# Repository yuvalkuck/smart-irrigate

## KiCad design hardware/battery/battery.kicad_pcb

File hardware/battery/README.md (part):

# Battery add-on board

Schematic: `battery.kicad_sch` (one sheet, all blocks wired pin to pin). The sheet carries only the wire-colour legend and the block titles.
All the notes are here. This folder has no PCB yet.

The battery board is an add-on for the battery stage. V1 of the system runs without it: the mainboard takes 24 V DC from an
external supply at its J1 and makes its own +5V and 24 VAC (`hardware/mainboard/README.md`). When the add-on is
installed, the external 24 V DC supply moves to the add-on J1, and the add-on J5 feeds the mainboard J1.
Nothing is on both boards: the add-on holds the battery, its gauge and protector, its charger and the 24 V DC bus that
keeps the mainboard running on battery.

## Rails and sources

| Output | Connector | Value | Source |
|---|---|---|---|
| 24 V DC to the mainboard | J5 | 23.9 V typical, rated 2 A | LM5176 buck-boost (U6) |
| Pack charge | J2 | 20.82 V typical, 0.498 A | BQ24610 charger (U4) |

## How power flows

```
24 V PSU -- J1 -- F1 -- ideal diode U1/Q1 --+-- BUS (14 to 25 V)
                                             |
pack 5S -- J2 -- F2 -- Q3 (CHG) -- Q4 (DSG) -- PACKP -- ideal diode U2/Q2 --+
   B- (VSS) -- R69 (2 mohm) -- GND   (BQ40Z80 U3 drives Q3 and Q4, counts the current in R69)
                                             |
BUS --+-- U4 charger (21 V, 0.5 A) ----------> PACKP -> pack
      +-- U6 buck-boost -------------------> +24V (J5) -> mainboard J1
```

* The pack is 5S so that its full voltage (5 x 4.2 V = 21 V) stays below the 24 V supply. The two ideal diodes then switch sources by themselves, with no relay.
* BUS range is 14 V to 25 V. The lower limit is the cell under-voltage cut (2.8 V x 5 cells = 14 V); the BQ40Z80 limits are set in its data flash.
* U6 holds +24V at 23.9 V over the whole bus range, so the mainboard sees the same 24 V on mains and on battery.
* The charger is fed from BUS (after U1), not from the PSU node. It has no power-path mode, so the pack never feeds the PSU node through the charger.
* On mains, the charger takes only the 0.5 A set by its sense resistor R18. U6 takes the rest from the PSU through the same bus.
* Q3 and Q4 are high-side N-FETs with their drains joined in the middle (`MID`), as in the BQ40Z80 datasheet: CHG drives Q3 against the cell-stack side, DSG drives Q4 against the pack side.

## Connectors

| Ref | Pins | Use |
|---|---|---|
| J1 | 1 = 24 V in, 2 = GND | external 24 V DC supply |
| J2 | 1 = pack B+ (`BP`), 2 = pack B- (`VSS`) | pack power |
| J3 | 1 = B-, 2 to 5 = cell taps 1 to 4, 6 = B+, 7 = gauge `TS1`, 8 = charger `TS`, 9 = GND | pack sense (1x9 pin header, 2.54 mm): balance taps and the two 10 k NTCs (103AT) |
| J4 | 1 = +5V (from the mainboard), 2 = GND, 3 = +3V3 (from the mainboard), 4 = SDA, 5 = SCL, 6 = `MAINS_OK_N`, 7 = `STAT1`, 8 = `STAT2` | link to mainboard J16 (1x8 pin header, 2.54 mm, same pin order) |
| J5 | 1 = +24V, 2 = GND | 24 V DC out to mainboard J1 |

Pack B- (`VSS`) is not the same net as GND: the 2 mohm sense resistor R69 sits between them.
The gauge NTC returns to J3 pin 1 (B-), the charger NTC to J3 pin 9 (GND).

### Wiring the pack to J3

The pack is 5 cells in series (5S), cell 1 at the negative end. J3 only senses; the charge and discharge current goes through J2 (pin 1 = B+, pin 2 = B-).

| J3 pin | Connect to | Net, and where it goes |
|---|---|---|
| 1 | pack negative (cell 1 minus) | `VSS`, the same net as J2 pin 2; BQ40Z80 `VSS` |
| 2 | cell 1 plus (= cell 2 minus) | R64 to `VC1` |
| 3 | cell 2 plus (= cell 3 minus) | R65 to `VC2` |
| 4 | cell 3 plus (= cell 4 minus) | R66 to `VC3` |
| 5 | cell 4 plus (= cell 5 minus) | R67 to `VC4` |
| 6 | pack positive (cell 5 plus) | `BP`, the same net as J2 pin 1; R68 to `VC5` |
| 7 | one lead of the gauge NTC (10 k, 103AT); the other lead goes to pin 1 | BQ40Z80 `TS1` |
| 8 | one lead of the charger NTC (10 k, 103AT); the other lead goes to pin 9 | BQ24610 `TS`, with R25 and R26 |
| 9 | the other lead of the charger NTC | GND |

* Both NTCs sit on the pack.
* `VC6` of the BQ40Z80 is tied to `VC5`, so only the taps above are used.

## What the hardware reports to the mainboard

| Metric | Source | Reaches the mainboard on |
|---|---|---|
| Each cell voltage (5 cells), pack voltage | BQ40Z80, cell taps VC1 to VC5 | SMBus: J4 pins 4 and 5 |
| Pack current, both directions | BQ40Z80, coulomb counter on R69 | SMBus |
| Charge amount (remaining capacity, state of charge, full-charge capacity, cycle count) | BQ40Z80, Impedance Track gas gauge | SMBus (datasheet: "available capacity, voltage, current, temperature, and other critical parameters") |
| Pack temperature | BQ40Z80 `TS1` (the NTC on J3 pin 7); `TS2` to `TS4` are free | SMBus |
| Protection status (OV, UV, overcurrent, short circuit, temperature) | BQ40Z80 | SMBus |
| Charger state: charging, done, fault | BQ24610 `STAT1` and `STAT2` (open drain) | J4 pins 7 and 8 (pull-ups R65 and R66 are on the mainboard) |
| Mains present | BQ24610 `PG` (open drain) | J4 pin 6 (`MAINS_OK_N`, pull-up R64 on the mainboard) |

* `MAINS_OK_N`: low means BUS is above the pack, which means the supply is present. High means battery. If the pin sticks high, firmware sees "battery", which is the safe side.
* The BQ40Z80 SMBus pins (`SMBD`, `SMBC`) accept 1.3 V as high and 0.8 V as low (datasheet, electrical characteristics), so the 3.3 V pull-ups on the mainboard I2C bus are enough. Its SMBus speed is 10 to 100 kHz in slave mode, so the shared mainboard bus has to run at 100 kHz or below.
* The BQ40Z80 SMBus slave address is in its technical reference manual (SLUUBT5), which I have not read.
* Firmware items that follow from this (not changed here): read `MAINS_OK_N`, `STAT1` and `STAT2`, apply the 2-valve limit while `MAINS_OK_N` is high, and read the BQ40Z80 over SMBus.

## Block values

Source tags: D = value or part taken from the datasheet. C = computed with that datasheet's equation. T = start value, tune on the bench.

### Input and bus
* F1 is a 10 A 5x20 fuse at the input. U1/Q1 (PSU) and U2/Q2 (pack) are LM74700-Q1 ideal-diode controllers with DMT6007LFG FETs. C1 to C4 are the 100 nF charge-pump and anode capacitors (D).
* Bus capacitors: C5 220 uF polymer and C6 to C9, 4 x 10 uF.

### Battery gauge and protector (U3, BQ40Z80)
* 2-series to 6-series pack manager with gas gauging, protection, cell balancing and SMBus, VQFN-32 (datasheet SLUSBV4D). Used as 5S: `VC6` is tied to `VC5` ("if not used, connect to VC5", D).
* Cell taps: R64 to R68 (100 R) and C94 to C98 (100 nF) on `VC1` to `VC5`, as in the datasheet (D). The internal balancing FETs are 200 R, so the 100 R series resistors set the balance current (D).
* Current: R69 is a 2 mohm 1 W 50 ppm sense resistor in the pack minus lead, between `VSS` (the cell stack) and GND. The datasheet supports 1 to 3 mohm and wants 50 ppm or better (D). R70 and R71 (100 R) with C99 (100 pF) and C100/C101 (100 nF) filter `SRP` and `SRN` (D).
* Supply: `BAT` from `BP` through D5 and R72 (100 R); `VCC` from the middle of the FETs through D6 and R73 (100 R); `PACK` from the pack side through R74 (100 R). C102 (2.2 uF) on `PBI` (D). The two diodes and the series values are start values (T).
* FETs: Q3 (charge) and Q4 (discharge) are DMT6007LFG, 60 V. Gate resistors R75 and R77 (10 k) and gate-source resistors R76 and R78 (10 M), as in the datasheet (D). C103 and C104 (100 nF in series) across the pack terminals are the datasheet ESD pair.
* Temperature: the pack NTC (J3 pin 7) is on `TS1`. The BQ40Z80 has an internal 18 k pull-up for a 10 k 103 NTC (D), so no bias resistor is fitted.
* Unused pins: `TS2`, `TS3`, `TS4`, `DISP`, `PDSG`, `PRES`, `FUSE` are tied to `VSS` ("connect directly to VSS and configure data flash accordingly", D). `LEDCNTLA/B/C` go to `VSS` through R79, R80 and R81, 20 k each ("if not used, connect to VSS with a 20-kΩ resistor", D). `PCHG` is left open ("leave floating if not used", D). The pre-charge FET and the chemical fuse are not used.
* F2 is the 10 A fuse in the pack plus lead, between `BP` and the charge FET.
* One-time setup: the chip must be configured with TI bqStudio (cell count, chemistry, calibration; datasheet section 7.3.1) before the gauge readings are valid.

### Charger (U4, BQ24610)
* Charge voltage: R19 (909 k) and R20 (102 k), both 0.1 %, give 20.82 V typical, which is 4.16 V per cell. The worst case with tolerances is 20.96 V (4.19 V per cell). (C)
* Charge current: R18 (100 m) with ISET1 at 1.00 V gives about 0.50 A (R21 100 k over R22 43.2 k set 0.498 A). (C)
* Termination and pre-charge: R23 100 k over R24 17.8 k set about 49.9 mA. (C)
* C30 (100 nF) on `TTC` sets the safety timer to about 9.3 h. (D)
* NTC window 0 to 45 C: R25 9.31 k, R26 430 k, NTC at J3 pin 8. (D)
* L1 6.8 uH, Q5 (dual DMN6040SSD) as the two switches, D1 and C26 as the bootstrap.
* `STAT1` and `STAT2` (open drain) go to J4. The power-path pins and the input-current regulation are not used. This follows the BQ24610 datasheet's typical application without power path (section 10.2.2).

### 24 V DC (U6, LM5176)
* Input 14 V to 25 V, output 23.9 V (R36 309 k over R37 10.7 k), switching about 297 kHz (R32 27.4 k). L3 15 uH. (C)
* R29 is the 15 m sense resistor. The minimum boost current limit is about 6.7 A against a peak need of about 4.6 A at 2 A load. (C)
* Compensation R33 5.76 k, C40 82 nF, C41 680 pF, slope C38 390 pF, soft start C39 100 nF are start values. (T)
* Under-voltage lock-out: R34 249 k over R35 29.4 k turns it on at about 11.55 V (1.22 V typical `EN/UVLO` threshold). R38 (93.1 k) sets the hiccup mode.
* Q6 to Q9 are the four DMT6007LFG switches, D2 and D3 with C45 and C46 are the two bootstraps.

### Test points, LEDs and mounting holes
* Test points (2.0 mm through-hole pads, as on the mainboard): TP1 GND, TP2 `PSU_IN`, TP3 `BUS`, TP4 `PACKP` (pack +), TP5 `VSS` (pack minus, so the drop across R69 can be read against GND), TP6 `+24V` (output to the mainboard).
* Power-on LED DS7 (5 mm green): `BUS` through R88 (10 k) to GND, about 2 mA. `BUS` is live from either the PSU or the pack, so it shows that the board is powered. It stays on, and on battery it draws about 2 mA.
* SW1 "SHOW LEDs" lights all the rail LEDs while it is pressed. The cathodes of DS1 to DS6 are joined, and SW1 connects that node to GND. Nothing is drawn while the button is up. Each LED has a series resistor from its rail:

| LED (0805 red) | Rail | Resistor |
|---|---|---|
| DS1 | `PSU_IN` | R82, 10 k |
| DS2 | `BUS` | R83, 10 k |
| DS3 | `PACKP` | R84, 10 k |
| DS4 | `+24V` | R85, 10 k |
| DS5 | `+5V` (from the mainboard, J4) | R86, 1 k |
| DS6 | `+3V3` (from the mainboard, J4) | R87, 470 R |

* The resistor values are start values (T). I did not check the LED brightness on the bench.
* H1 to H4 are four M3 mounting holes (`MountingHole_3.2mm_M3`), with no net. The schematic has no PCB yet, so their positions are not set.
* The rails reach this block through net labels (`PSU_IN`, `BUS`, `PACKP`, `VSS`, `+24V`); `+5V` and `+3V3` are power symbols.

## Bill of materials (grouped by value)

Counts come from the schematic. Resistors and capacitors are 0805 unless the footprint says otherwise.
Reference numbers have gaps: the 5 V, 12 V, 45 V boost and inverter parts moved to the mainboard, and the BQ7791501 parts were replaced.

| Parts | Value / part | Footprint |
|---|---|---|
| U1, U2 | LM74700QDBVRQ1 | SOT-23-6 |
| U3 | BQ40Z80RSMR | VQFN-32 4x4 |
| U4 | BQ24610RGER | VQFN-24 |
| U6 | LM5176PWPR | HTSSOP-28 |
| Q1, Q2, Q3, Q4, Q6, Q7, Q8, Q9 | DMT6007LFG | PowerDI3333-8 |
| Q5 | DMN6040SSD-13 (dual) | SOIC-8 |
| D1, D2, D3, D5, D6 | MBR0540 | SOD-123 |
| L1 | 6.8 uH Coilcraft XAL1010-682ME | XAL1010 |
| L3 | 15 uH Coilcraft XAL1010-153ME | XAL1010 |
| F1, F2 | 10 A fuse, 5x20 holder | fuse holder |
| J1, J2, J5 | 2-pin screw terminal | 5.00 mm |
| J3 | 1x9 pin header | 2.54 mm |
| J4 | 1x8 pin header | 2.54 mm |
| TP1 to TP6 | test point pad | 2.0 mm THT, 1.0 mm drill |
| DS1 to DS6 | LED, red | 0805 |
| DS7 | LED, green | 5 mm THT |
| SW1 | push button "SHOW LEDs" | 6 mm THT |
| H1 to H4 | M3 mounting hole | 3.2 mm |

Capacitors:

| Parts | Value |
|---|---|
| C1 C2 C3 C4 C18 C19 C20 C25 C26 C42 C44 C103 C104 | 100 nF 50 V X7R (13) |
| C39 C45 C46 C94 C95 C96 C97 C98 C100 C101 | 100 nF 25 V X7R (10) |
| C30 | 100 nF 25 V X7R, 5 % |
| C27 C28 | 1 uF 25 V X7R |
| C17 | 1 uF 50 V X7R |
| C43 | 1 uF 16 V X7R |
| C102 | 2.2 uF 50 V X7R |
| C6 C7 C8 C9 C47 C48 C49 C50 C51 C52 C53 | 10 uF 50 V X7R, 1210 (11) |
| C21 C22 | 10 uF 35 V X7R, 1210 |
| C23 C24 | 4.7 uF 50 V X7R, 1210 |
| C5 | 220 uF 35 V polymer, 8x10 |
| C54 | 100 uF 35 V polymer, 8x10 |
| C40 | 82 nF |
| C37 C38 C41 | 47 pF / 390 pF / 680 pF |
| C29 / C99 | 22 pF / 100 pF |

Resistors:

| Parts | Value |
|---|---|
| R69 | 2 m 1 % 1 W 50 ppm, 2512 |
| R29 | 15 m 1 % 1 W, 2512 |
| R18 | 100 m 1 % 0.5 W, 1206 |
| R17, R39 | 10 R |
| R30 R31 R64 R65 R66 R67 R68 R70 R71 R72 R73 R74 | 100 R (12) |
| R87 | 470 R |
| R86 | 1 k |
| R33 | 5.76 k |
| R25 | 9.31 k |
| R75, R77, R82, R83, R84, R85, R88 | 10 k |
| R37 | 10.7 k |
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
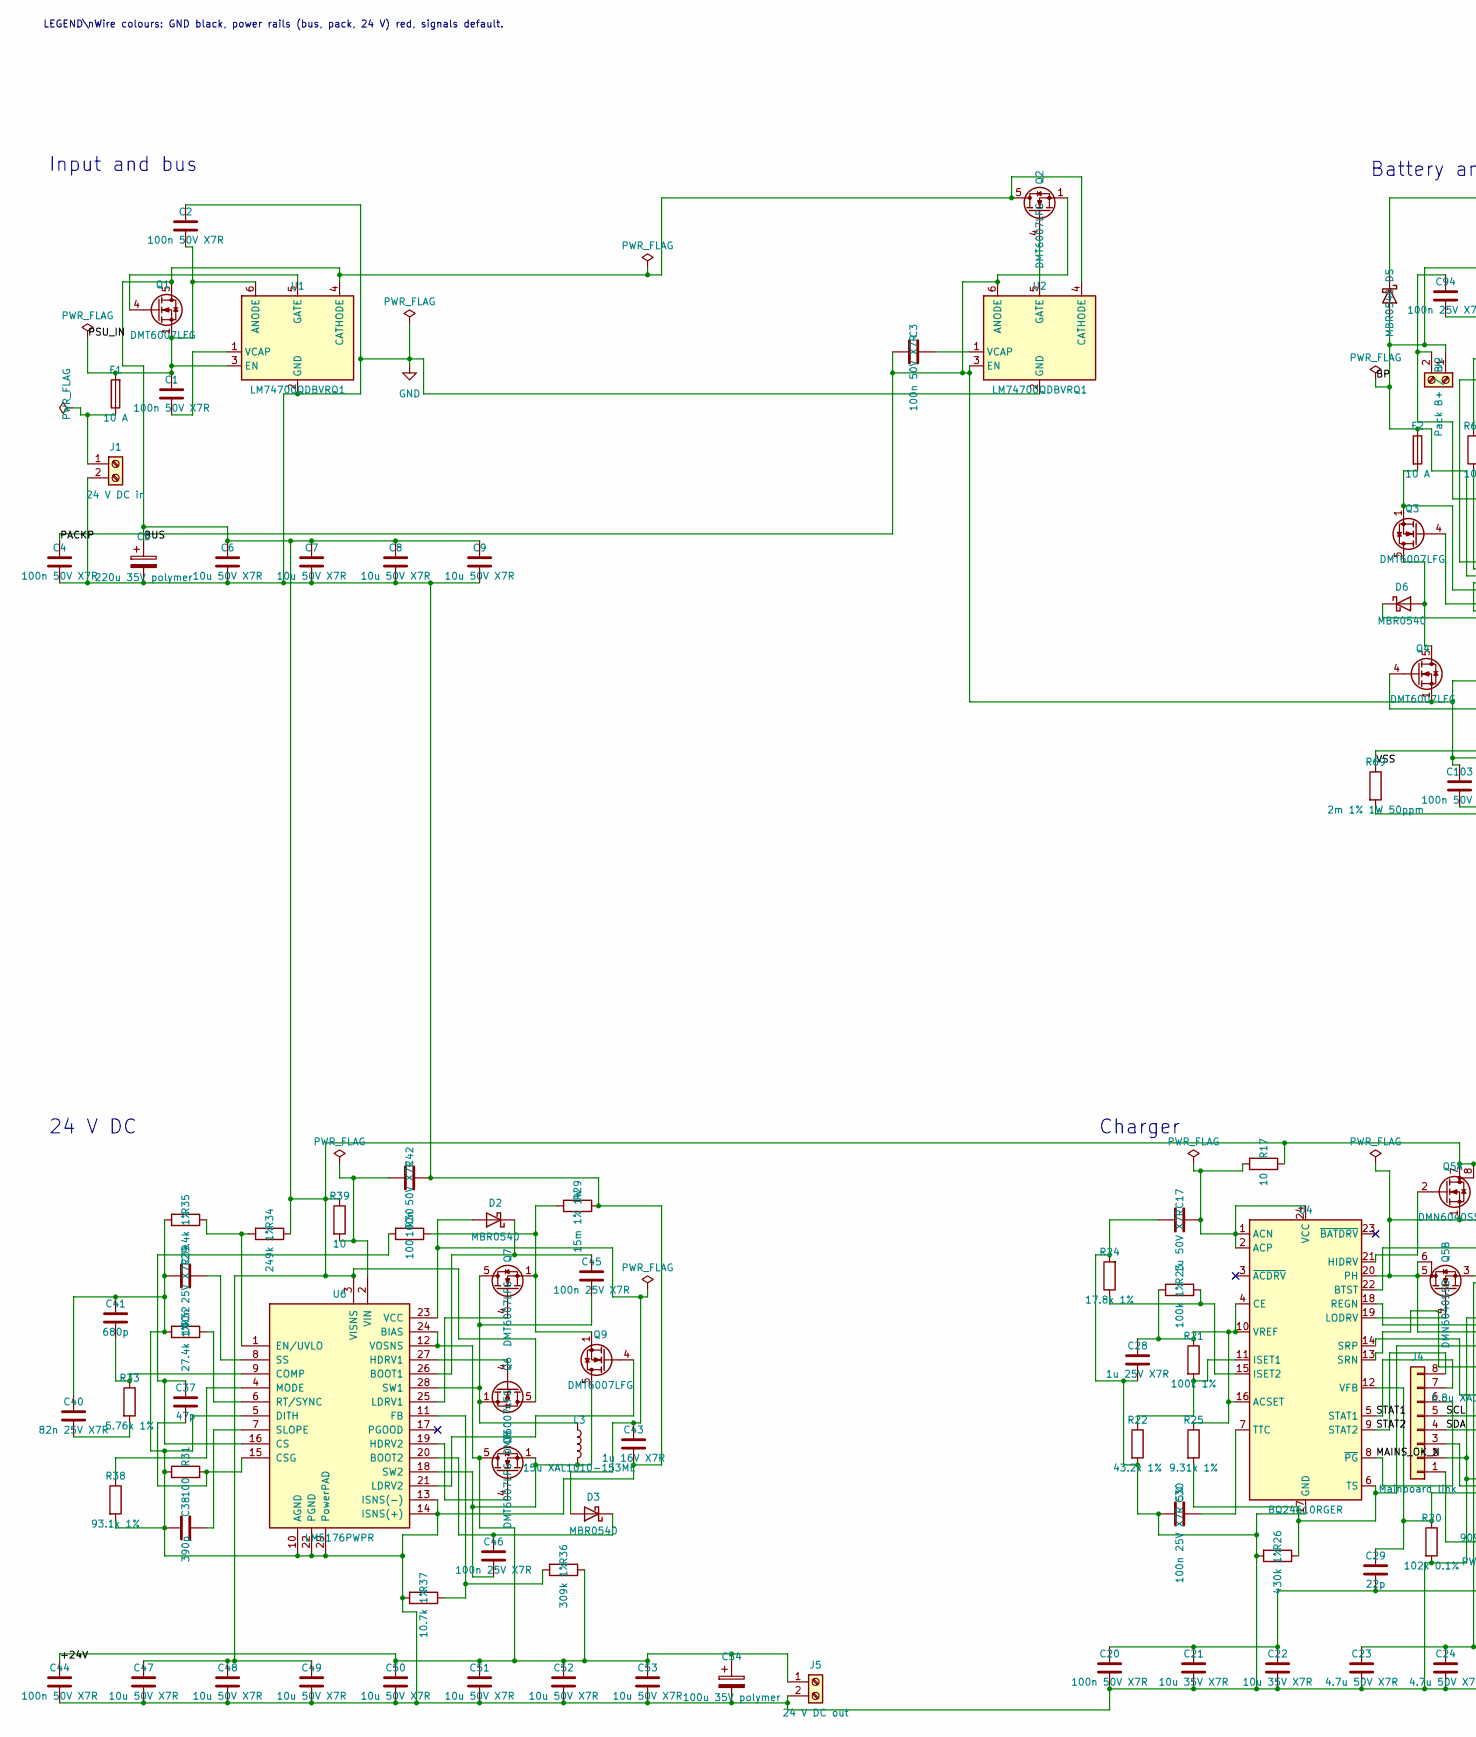
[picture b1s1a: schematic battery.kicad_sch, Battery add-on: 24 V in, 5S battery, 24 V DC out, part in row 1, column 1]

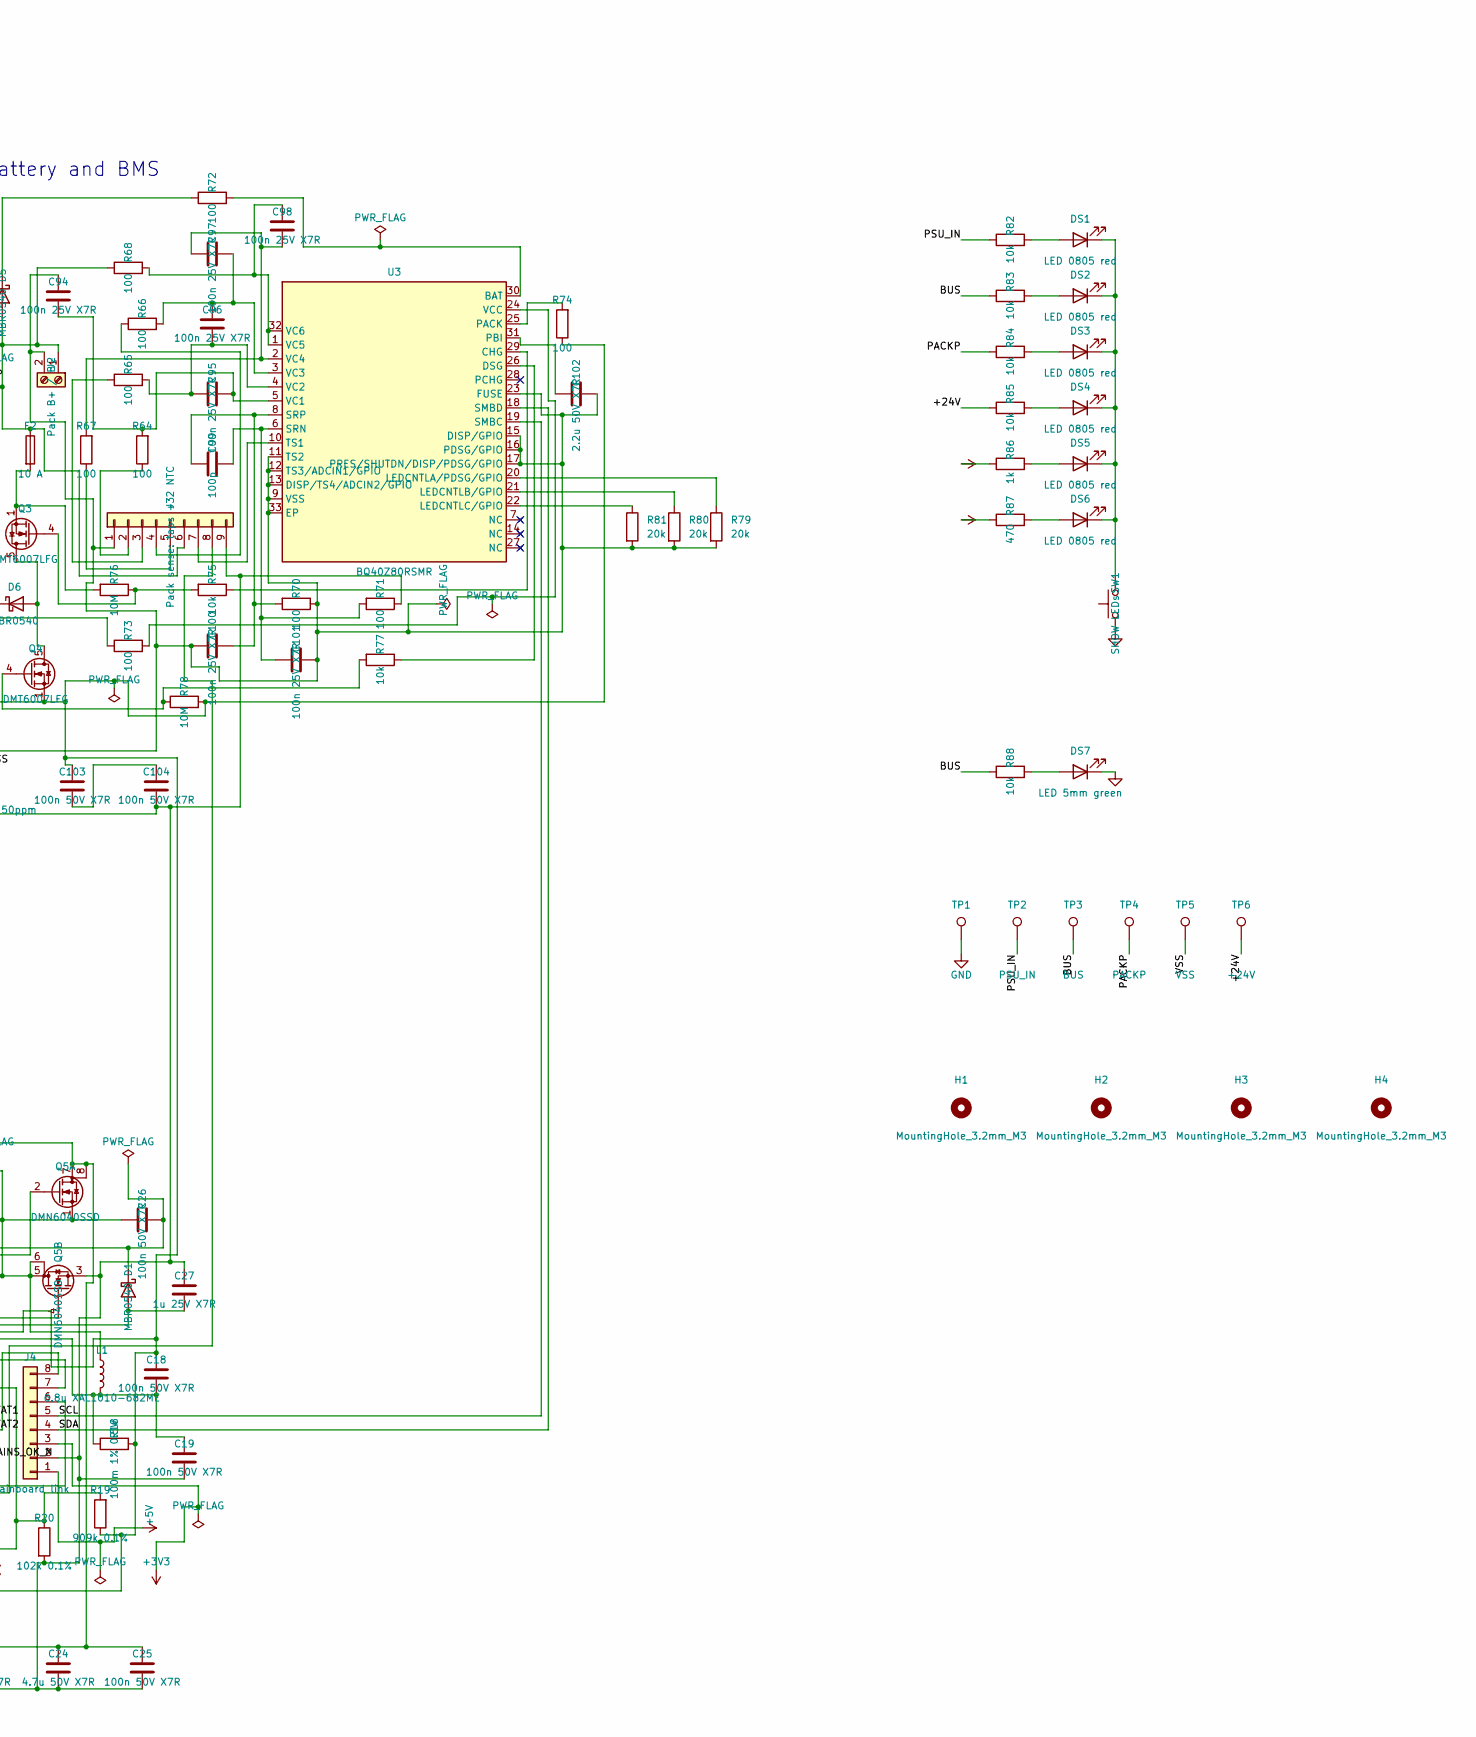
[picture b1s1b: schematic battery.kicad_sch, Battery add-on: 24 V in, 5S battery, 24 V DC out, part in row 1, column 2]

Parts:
C1, C2, C3, C4, C18, C19, C20, C25, C26, C42, C44, C103, C104: 100n 50V X7R
C5: 220u 35V polymer
C6, C7, C8, C9, C47, C48, C49, C50, C51, C52, C53: 10u 50V X7R
C17: 1u 50V X7R
C21, C22: 10u 35V X7R
C23, C24: 4.7u 50V X7R
C27, C28: 1u 25V X7R
C29: 22p
C30: 100n 25V X7R 5%
C37: 47p
C38: 390p
C39, C45, C46, C94, C95, C96, C97, C98, C100, C101: 100n 25V X7R
C40: 82n 25V X7R
C41: 680p
C43: 1u 16V X7R
C54: 100u 35V polymer
C99: 100p
C102: 2.2u 50V X7R
D1, D2, D3, D5, D6: MBR0540
DS1, DS2, DS3, DS4, DS5, DS6: LED 0805 red
DS7: LED 5mm green
F1, F2: 10 A
H1, H2, H3, H4: MountingHole_3.2mm_M3
J1: 24 V DC in
J2: Pack B+ / B-
J3: Pack sense: taps + 2 NTC
J4: Mainboard link
J5: 24 V DC out
L1: 6.8u XAL1010-682ME
L3: 15u XAL1010-153ME
Q1, Q2, Q3, Q4, Q6, Q7, Q8, Q9: DMT6007LFG; Diodes_PowerDI3333-8
Q5: DMN6040SSD
R17, R39: 10
R18: 100m 1% 0.5W
R19: 909k 0.1%
R20: 102k 0.1%
R21, R23: 100k 1%
R22: 43.2k 1%
R24: 17.8k 1%
R25: 9.31k 1%
R26: 430k 1%
R29: 15m 1% 1W
R30, R31, R64, R65, R66, R67, R68, R70, R71, R72, R73, R74: 100
R32: 27.4k 1%
R33: 5.76k 1%
R34: 249k 1%
R35: 29.4k 1%
R36: 309k 1%
R37: 10.7k 1%
R38: 93.1k 1%
R69: 2m 1% 1W 50ppm
R75, R77, R82, R83, R84, R85, R88: 10k
R76, R78: 10M
R79, R80, R81: 20k
R86: 1k
R87: 470
SW1: SHOW LEDs
TP1: GND
TP2: PSU_IN
TP3: BUS
TP4: PACKP
TP5: VSS
TP6: +24V
U1, U2: LM74700QDBVRQ1; SOT-23-6
U3: BQ40Z80RSMR; VQFN-32-1EP_4x4mm_P0.4mm_EP2.8x2.8mm
U4: BQ24610RGER; VQFN-24-1EP_4x4mm_P0.5mm_EP2.45x2.45mm
U6: LM5176PWPR; HTSSOP-28-1EP_4.4x9.7mm_P0.65mm_EP3.4x9.5mm_ThermalVias

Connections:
+3V3: J4.3, R87.1
+5V: J4.1, R86.1
/+24V: C44.1, C50.1, C51.1, C52.1, C53.1, C54.1, J5.1, Q8.5 (D), R36.1, R85.1, TP6.1 (1_1), U6.12 (VOSNS), U6.24 (BIAS)
/BP: D5.2 (A), F2.1, J2.1, J3.6, R68.1
/BUS: C5.1, C6.1, C7.1, C8.1, C9.1, C23.1, C24.1, C25.1, C47.1, C48.1, C49.1, Q1.5 (D), Q2.5 (D), Q5.7 (D), Q5.8 (D), Q6.5 (D), R17.1, R34.1, R39.1, R83.1, R88.1, TP3.1 (1_1), U1.4 (CATHODE), U2.4 (CATHODE), U6.3 (VISNS)
/MAINS_OK_N: J4.6, U4.8 (~PG)
/PACKP: C3.1, C4.1, C18.2, C20.1, C21.1, C22.1, C29.1, C103.1, Q2.1 (S), Q2.2 (S), Q2.3 (S), Q4.1 (S), Q4.2 (S), Q4.3 (S), R18.2, R19.1, R74.1, R78.2, R84.1, TP4.1 (1_1), U2.3 (EN), U2.6 (ANODE), U4.13 (SRN)
/PSU_IN: C1.1, C2.1, F1.2, Q1.1 (S), Q1.2 (S), Q1.3 (S), R82.1, TP2.1 (1_1), U1.3 (EN), U1.6 (ANODE)
/SCL: J4.5, U3.19 (SMBC)
/SDA: J4.4, U3.18 (SMBD)
/STAT1: J4.7, U4.5 (STAT1)
/STAT2: J4.8, U4.9 (STAT2)
/VSS: C94.2, C100.2, C101.2, C102.2, J2.2, J3.1, R69.1, R70.1, R79.2, R80.2, R81.2, TP5.1 (1_1), U3.9 (VSS), U3.11 (TS2), U3.12 (TS3/ADCIN1/GPIO), U3.13 (DISP/TS4/ADCIN2/GPIO), U3.15 (DISP/GPIO), U3.16 (PDSG/GPIO), U3.17 (PRES/SHUTDN/DISP/PDSG/GPIO), U3.23 (FUSE), U3.33 (EP)
GND: C2.2, C4.2, C5.2, C6.2, C7.2, C8.2, C9.2, C17.2, C19.2, C20.2, C21.2, C22.2, C23.2, C24.2, C25.2, C27.2, C28.2, C30.2, C38.2, C39.2, C40.2, C41.2, C42.2, C43.2, C44.2, C47.2, C48.2, C49.2, C50.2, C51.2, C52.2, C53.2, C54.2, C104.2, DS7.1 (K), J1.2, J3.9, J4.2, J5.2, Q5.3 (S), R20.2, R22.2, R24.2, R26.2, R29.2, R31.1, R32.2, R35.2, R37.2, R38.2, R69.2, R71.1, SW1.1, TP1.1 (1_1), U1.2 (GND), U2.2 (GND), U4.17 (GND), U4.25 (GND), U6.5 (DITH), U6.10 (AGND), U6.13 (ISNS(-)), U6.14 (ISNS(+)), U6.22 (PGND), U6.29 (PowerPAD)
unnamed: C40.1, R33.2
unnamed: C103.2, C104.1
unnamed: C27.1, D1.2 (A), U4.18 (REGN)
unnamed: C26.1, D1.1 (K), U4.22 (BTST)
unnamed: C43.1, D2.2 (A), D3.2 (A), U6.23 (VCC)
unnamed: C45.1, D2.1 (K), U6.26 (BOOT1)
unnamed: C46.1, D3.1 (K), U6.20 (BOOT2)
unnamed: D5.1 (K), R72.1
unnamed: D6.2 (A), Q3.5 (D), Q4.5 (D)
unnamed: D6.1 (K), R73.1
unnamed: DS1.2 (A), R82.2
unnamed: DS1.1 (K), DS2.1 (K), DS3.1 (K), DS4.1 (K), DS5.1 (K), DS6.1 (K), SW1.2
unnamed: DS2.2 (A), R83.2
unnamed: DS3.2 (A), R84.2
unnamed: DS4.2 (A), R85.2
unnamed: DS5.2 (A), R86.2
unnamed: DS6.2 (A), R87.2
unnamed: DS7.2 (A), R88.2
unnamed: F2.2, Q3.1 (S), Q3.2 (S), Q3.3 (S), R76.2
unnamed: F1.1, J1.1
unnamed: J3.2, R64.1
unnamed: J3.3, R65.1
unnamed: J3.4, R66.1
unnamed: J3.5, R67.1
unnamed: J3.7, U3.10 (TS1)
unnamed: J3.8, R25.2, R26.1, U4.6 (TS)
unnamed: Q1.4 (G), U1.5 (GATE)
unnamed: Q2.4 (G), U2.5 (GATE)
unnamed: Q3.4 (G), R75.2, R76.1
unnamed: Q4.4 (G), R77.2, R78.1
unnamed: Q5.2 (G), U4.21 (HIDRV)
unnamed: C26.2, L1.1, Q5.1 (S), Q5.5 (D), Q5.6 (D), U4.20 (PH)
unnamed: Q5.4 (G), U4.19 (LODRV)
unnamed: Q6.4 (G), U6.27 (HDRV1)
unnamed: C45.2, L3.1, Q6.1 (S), Q6.2 (S), Q6.3 (S), Q7.5 (D), U6.28 (SW1)
unnamed: Q7.4 (G), U6.25 (LDRV1)
unnamed: Q7.1 (S), Q7.2 (S), Q7.3 (S), Q9.1 (S), Q9.2 (S), Q9.3 (S), R29.1, R30.1
unnamed: Q8.4 (G), U6.19 (HDRV2)
unnamed: C46.2, L3.2, Q8.1 (S), Q8.2 (S), Q8.3 (S), Q9.5 (D), U6.18 (SW2)
unnamed: Q9.4 (G), U6.21 (LDRV2)
unnamed: C1.2, U1.1 (VCAP)
unnamed: C3.2, U2.1 (VCAP)
unnamed: R72.2, U3.30 (BAT)
unnamed: R75.1, U3.29 (CHG)
unnamed: R77.1, U3.26 (DSG)
unnamed: R79.1, U3.20 (LEDCNTLA/PDSG/GPIO)
unnamed: R80.1, U3.21 (LEDCNTLB/GPIO)
unnamed: R81.1, U3.22 (LEDCNTLC/GPIO)
unnamed: R74.2, U3.25 (PACK)
unnamed: C102.1, U3.31 (PBI)
unnamed: C99.2, C101.1, R71.2, U3.6 (SRN)
unnamed: C99.1, C100.1, R70.2, U3.8 (SRP)
unnamed: C94.1, C95.2, R64.2, U3.5 (VC1)
unnamed: C95.1, C96.2, R65.2, U3.4 (VC2)
unnamed: C96.1, C97.2, R66.2, U3.3 (VC3)
unnamed: C97.1, C98.2, R67.2, U3.2 (VC4)
unnamed: C98.1, R68.2, U3.1 (VC5), U3.32 (VC6)
unnamed: R73.2, U3.24 (VCC)
unnamed: C17.1, R17.2, U4.1 (ACN), U4.2 (ACP), U4.24 (VCC)
unnamed: C28.1, R21.1, R23.1, R25.1, U4.4 (CE), U4.10 (VREF), U4.16 (ACSET)
unnamed: R21.2, R22.1, U4.11 (ISET1)
unnamed: R23.2, R24.1, U4.15 (ISET2)
unnamed: C18.1, C19.1, L1.2, R18.1, U4.14 (SRP)
unnamed: C30.1, U4.7 (TTC)
unnamed: C29.2, R19.2, R20.1, U4.12 (VFB)
unnamed: C41.1, R33.1, U6.9 (COMP)
unnamed: C37.1, R30.2, U6.16 (CS)
unnamed: C37.2, R31.2, U6.15 (CSG)
unnamed: R34.2, R35.1, U6.1 (EN/UVLO)
unnamed: R36.2, R37.1, U6.11 (FB)
unnamed: R38.1, U6.4 (MODE)
unnamed: R32.1, U6.6 (RT/SYNC)
unnamed: C38.1, U6.7 (SLOPE)
unnamed: C39.1, U6.8 (SS)
unnamed: C42.1, R39.2, U6.2 (VIN)

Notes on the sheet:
Input and bus
LEGEND\nWire colours: GND black, power rails (bus, pack, 24 V) red, signals default.
Charger
24 V DC
Battery and BMS

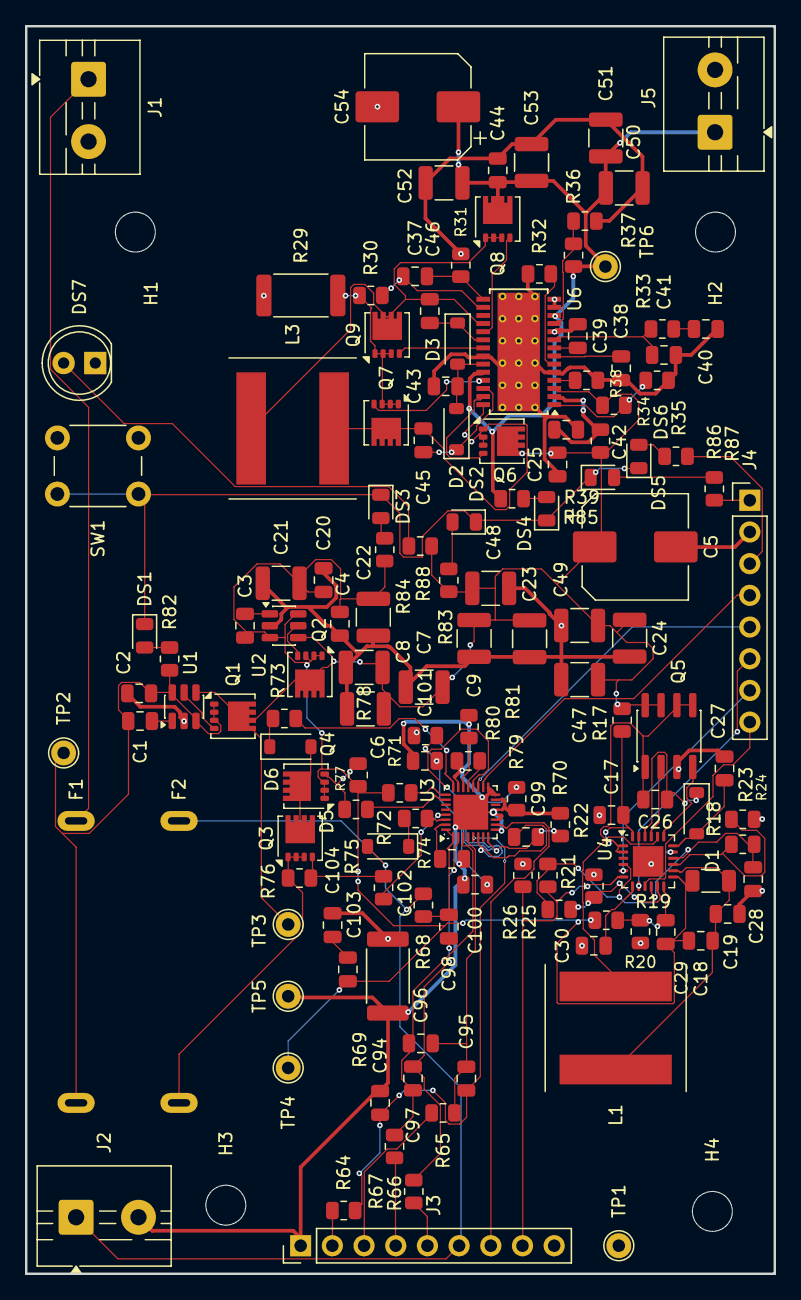
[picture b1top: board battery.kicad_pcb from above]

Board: 2 copper layers, 60.0 x 100.0 mm, 144 parts (0 on the bottom side), 89 nets.

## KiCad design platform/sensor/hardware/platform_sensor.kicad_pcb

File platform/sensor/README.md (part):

# Sensor Platform

Firmware project for the **sensor cluster**, the outdoor node on the sensor mast. It is a separate
STM32CubeMX project (`sensor_platform.ioc`), not part of the ESP-IDF build. The board is in
`hardware/kicad/`.

The node reads the local sensors and answers the ESP32-C6 over RS-485. The C6 is the Modbus master
and polls the cluster; the cluster never sends on its own.

## Hardware

| Item | Value |
|---|---|
| MCU | STM32C011F6P3TR (TSSOP-20, 32 KB flash, 6 KB RAM), matches `Mcu.CPN` in the `.ioc` |
| Clock | Internal, 12 MHz (as set in the `.ioc`) |
| Logic supply | 3.3 V from U3 (AP2112K-3.3), fed from the incoming 5 V |
| Bus transceiver | U2 MAX3485EPA (DIP-8) |
| Bus protection | D1 SM712 on A/B behind R11 and R12 (10 ohm, 1206, in series with A and B), D2 SMAJ5.0A on 5 V |
| Sensor-side protection | D6 SMAJ5.0A across AIN and GND, D7 and D8 (3.3 V bidirectional ESD diodes, SOD-523) on SDA and SCL |
| Cable shield | J1 and J4 pin 5 (SHLD) go to GND through R13 (1 M) in parallel with C9 (1 nF, 1 kV) |
| Input fuse | F1, 5x20 mm fuse (500 mA) in the ELECAPITAL PCB holder (footprint `libraries:FuseHolder_5x20_ELECAPITAL_PCB_Cover`), between the raw 5 V input and D2/FB1. J1.3 and J4.3 are before the fuse, so a daisy-chained node is not fused by this one. |
| Input filter | FB1 470 ohm ferrite on the 5 V, C8 47 uF bulk |
| Indicators | D3 green on 3.3 V (R10 1 k), D4 yellow on TX and D5 yellow on RX (R8, R9 1 k, lit when the line is low) |
| Wind input | J8 (library `WindSensor_0_5V`: 1 = +24V, 2 = GND, 3 = OUT). OUT goes through R14 (1.8 k) and R15 (3.3 k) to PA4, so 0-5 V becomes 0-3.24 V. D9 SMAJ30A on +24V, D10 SMAJ5.0A on OUT. The same wind sensor can instead connect to the mainboard. |
| Mode switch | SW1, 2-position DIP switch. Switch 1 fits the 120 ohm terminator R6 across A and B. Switch 2 pulls PA5 to GND to show that the wind sensor is fitted here. |
| Test points | TP1 +5V, TP2 +3V3, TP3 GND, TP4 A, TP5 B |
| Mounting | H1-H4, M3 holes (3.2 mm) |

Protection is for ESD and small induced surges only. A direct or very near lightning strike is not
covered: that needs a grounded mast with a lightning rod and the cable shield earthed at one end.

Power arrives from the main box on its own twisted pair. The board does not use 24 V itself. J1 and J4
pin 6 carry an optional +24V pass-through, for the wind sensor on J8 or for the next node. It is not
fused on this board, and it is left empty when no wind sensor is connected.

### Sensors

| Sensor | Interface | Purpose |
|---|---|---|
| SHT41 | I2C1 (J2, own connector) | Air temperature and relative humidity, for vapor pressure deficit |
| BMP581 | I2C1 (J7, own connector) | Barometric pressure and temperature, for rain-front prediction |
| Solar panel (0.3 W, 5 V polysilicon epoxy module) | ADC, PA0 (J6, own connector) | Sunlight level, for solar load |
| Wind sensor (3-cup, 0-30 m/s, 10-30 V supply, 0-5 V output) | ADC, PA4 (J8, own connector) | Wind speed. Optional: it can connect here or to the mainboard, selected by the hardware enable mask (`SensorWindPlatform`) |

The TSL2591 is dropped from the design. SHT41 and BMP581 sit in a ventilated radiation shield and
each connect over a short I2C cable, SHT41 to J2 and BMP581 to J7. The two connectors are in parallel on
the same I2C1 bus. I2C pull-ups (R1, R2, 4.7 k) go to 3.3 V, so both sensors run at 3.3 V logic.

## Pin map

From the netlist of `hardware/kicad/sensor-cluster.kicad_sch`.

| U1 pin | Function | Net |
|---|---|---|
| 1 | I2C1_SDA | J2 pin 4, J7 pin 2, R1 pull-up |
| 20 | I2C1_SCL | J2 pin 3, J7 pin 3, R2 pull-up |
| 7 (PA0) | ADC1_IN0 | Solar divider |
| 8 (PA1) | USART2_DE | U2 DE and /RE, R7 10 k to GND |
| 9 (PA2) | USART2_TX | U2 DI |
| 10 (PA3) | USART2_RX | U2 RO |
| 18 | SWDIO | J5 pin 2 |
| 19 | SWCLK | J5 pin 3 |
| 6 | NRST | J5 pin 4, C3 100 nF |
| 11 (PA4) | ADC input | Wind divider R14/R15 on J8 OUT, also on J3 pin 3 |
| 12 (PA5) | Input with pull-up | SW1 switch 2 to GND (ON = wind fitted), also on J3 pin 4 |
| 13-17, 2, 3 | unused | J3 breakout (PA6-PA10, PC14, PC15) |

DE and /RE are tied together and driven by the USART2 DE output (hardware driver-enable).

### Connectors

| Ref | Pins |
|---|---|
| J1 (6-pin terminal, 5.00 mm) | 1 = A, 2 = B, 3 = +5 V, 4 = GND, 5 = SHLD (cable shield), 6 = +24V (optional, wind sensor only) |
| J4 (6-pin terminal, 5.00 mm) | Same pins as J1, wired in parallel with it, to daisy-chain the bus to another node. The +5 V pin is the raw input, before D2 and FB1. |
| J8 (wind sensor terminal) | 1 = +24V, 2 = GND, 3 = OUT. The library footprint has 4 terminals, and terminal 4 has no net. |
| J2 (SHT41 module, library `SHT41_I2C_Module`) | 1 = VCC (3.3 V), 2 = GND, 3 = SCL, 4 = SDA |
| J7 (4-pin 2.54 mm row) | BMP581: 1 = GND, 2 = SDA, 3 = SCL, 4 = 3.3 V out |
| J6 (2-pin 2.54 mm row) | Solar panel, two wires: 1 = + (AIN), 2 = - (GND) |
| J5 (5-pin 2.54 mm row) | SWD programming: 1 = 3.3 V, 2 = SWDIO, 3 = SWCLK, 4 = NRST, 5 = GND |
| J3 (10-pin 2.54 mm row) | Breakout of the unused MCU pins: 1 = PC14, 2 = PC15, 3 = PA4, 4 = PA5, 5 = PA6, 6 = PA7, 7 = PA8, 8 = PA9, 9 = PA10, 10 = GND. 3.3 V only. |
| SW1 (2-position DIP switch) | Switch 1 (pins 1 and 4) fits the 120 ohm terminator R6 across A and B. Turn it on at the bus end only. Switch 2 (pins 2 and 3) pulls PA5 to GND when the wind sensor is fitted. |

Only AIN tolerates 5 V. SDA, SCL and the SWD pins are 3.3 V only.

### Solar input

The panel connects to J6 (AIN and GND). R5 (22 ohm, 1206, 0.25 W) across AIN and GND is the shunt, so
the panel current becomes a voltage. R3 (10 k) and R4 (15 k) divide it by 0.6 to the PA0 input, with
C7 (100 nF) as filter. Full scale at the pin is 3.0 V for 5.0 V at AIN. The panel current in watts is
only a relative sunlight measure, so calibrate it against a reference.

The panel is a generic DIY solar charger module. Specification from the listing:

| Item | Value |
|---|---|
| Power | 0.3 W |
| Material | Polycrystalline silicon, epoxy board |
| Voltage | 5 V |
| Operating current | 0-60 mA |
| Size | 68 x 36 mm |

The listing gives no open-circuit voltage. At the full 60 mA, R5 drops 1.32 V and dissipates about
80 mW, well inside its 0.25 W rating. PA0 then sees about 0.8 V, about 26 % of the 3.0 V full scale.
Keep this in mind when calibrating: a larger R5 would use more of the ADC range, but it also raises
the panel voltage, so it is not changed yet.

## Power consumption

Datasheet values, at the supply voltage stated for each row. Rows marked **not verified** have no figure
yet: the ST and Analog Devices sites would not serve the datasheet. The board has not been measured.

| Part | Condition | Current | Source |
|---|---|---|---|
| U3 AP2112K-3.3 | Quiescent, no load, VIN = 2.5 V | 55 uA typ, 80 uA max | Diodes AP2112 datasheet |
| SHT41 | Idle | 0.1 uA typ, 1.0 uA max (25 C) | Sensirion SHT4x datasheet |
| SHT41 | While measuring | 350 uA typ, 500 uA max | Sensirion SHT4x datasheet |
| SHT41 | Average, one measurement per second | 0.4 uA (medium repeatability) to 2.4 uA (high) | Sensirion SHT4x datasheet |
| BMP581 | Standby (25 C) | 1.0 uA | Bosch BMP581 datasheet |
| BMP581 | Low-power mode, 1 Hz | 1.3 uA | Bosch BMP581 datasheet |
| U1 STM32C011F6P3TR | Run at 12 MHz | **not verified** | ST datasheet |
| U2 MAX3485EPA | Supply current, driver on and off | **not verified** | Analog Devices datasheet |
| D3 green LED | Always on, R10 1 k | about 1.3 mA | Calculated, assumes 2 V forward voltage |
| D4, D5 yellow LEDs | Only while TX or RX is low, R8 and R9 1 k | about 1.3 mA each while lit | Calculated, assumes 2 V forward voltage |

All parts except the 5 V pair are fed from 3.3 V through U3, so the 5 V current at J1 is the sum of
these plus U3's own quiescent current (a linear regulator passes the load current through).

The total is not computed because U1 and U2 are missing. Measure it on the built board with a meter in
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
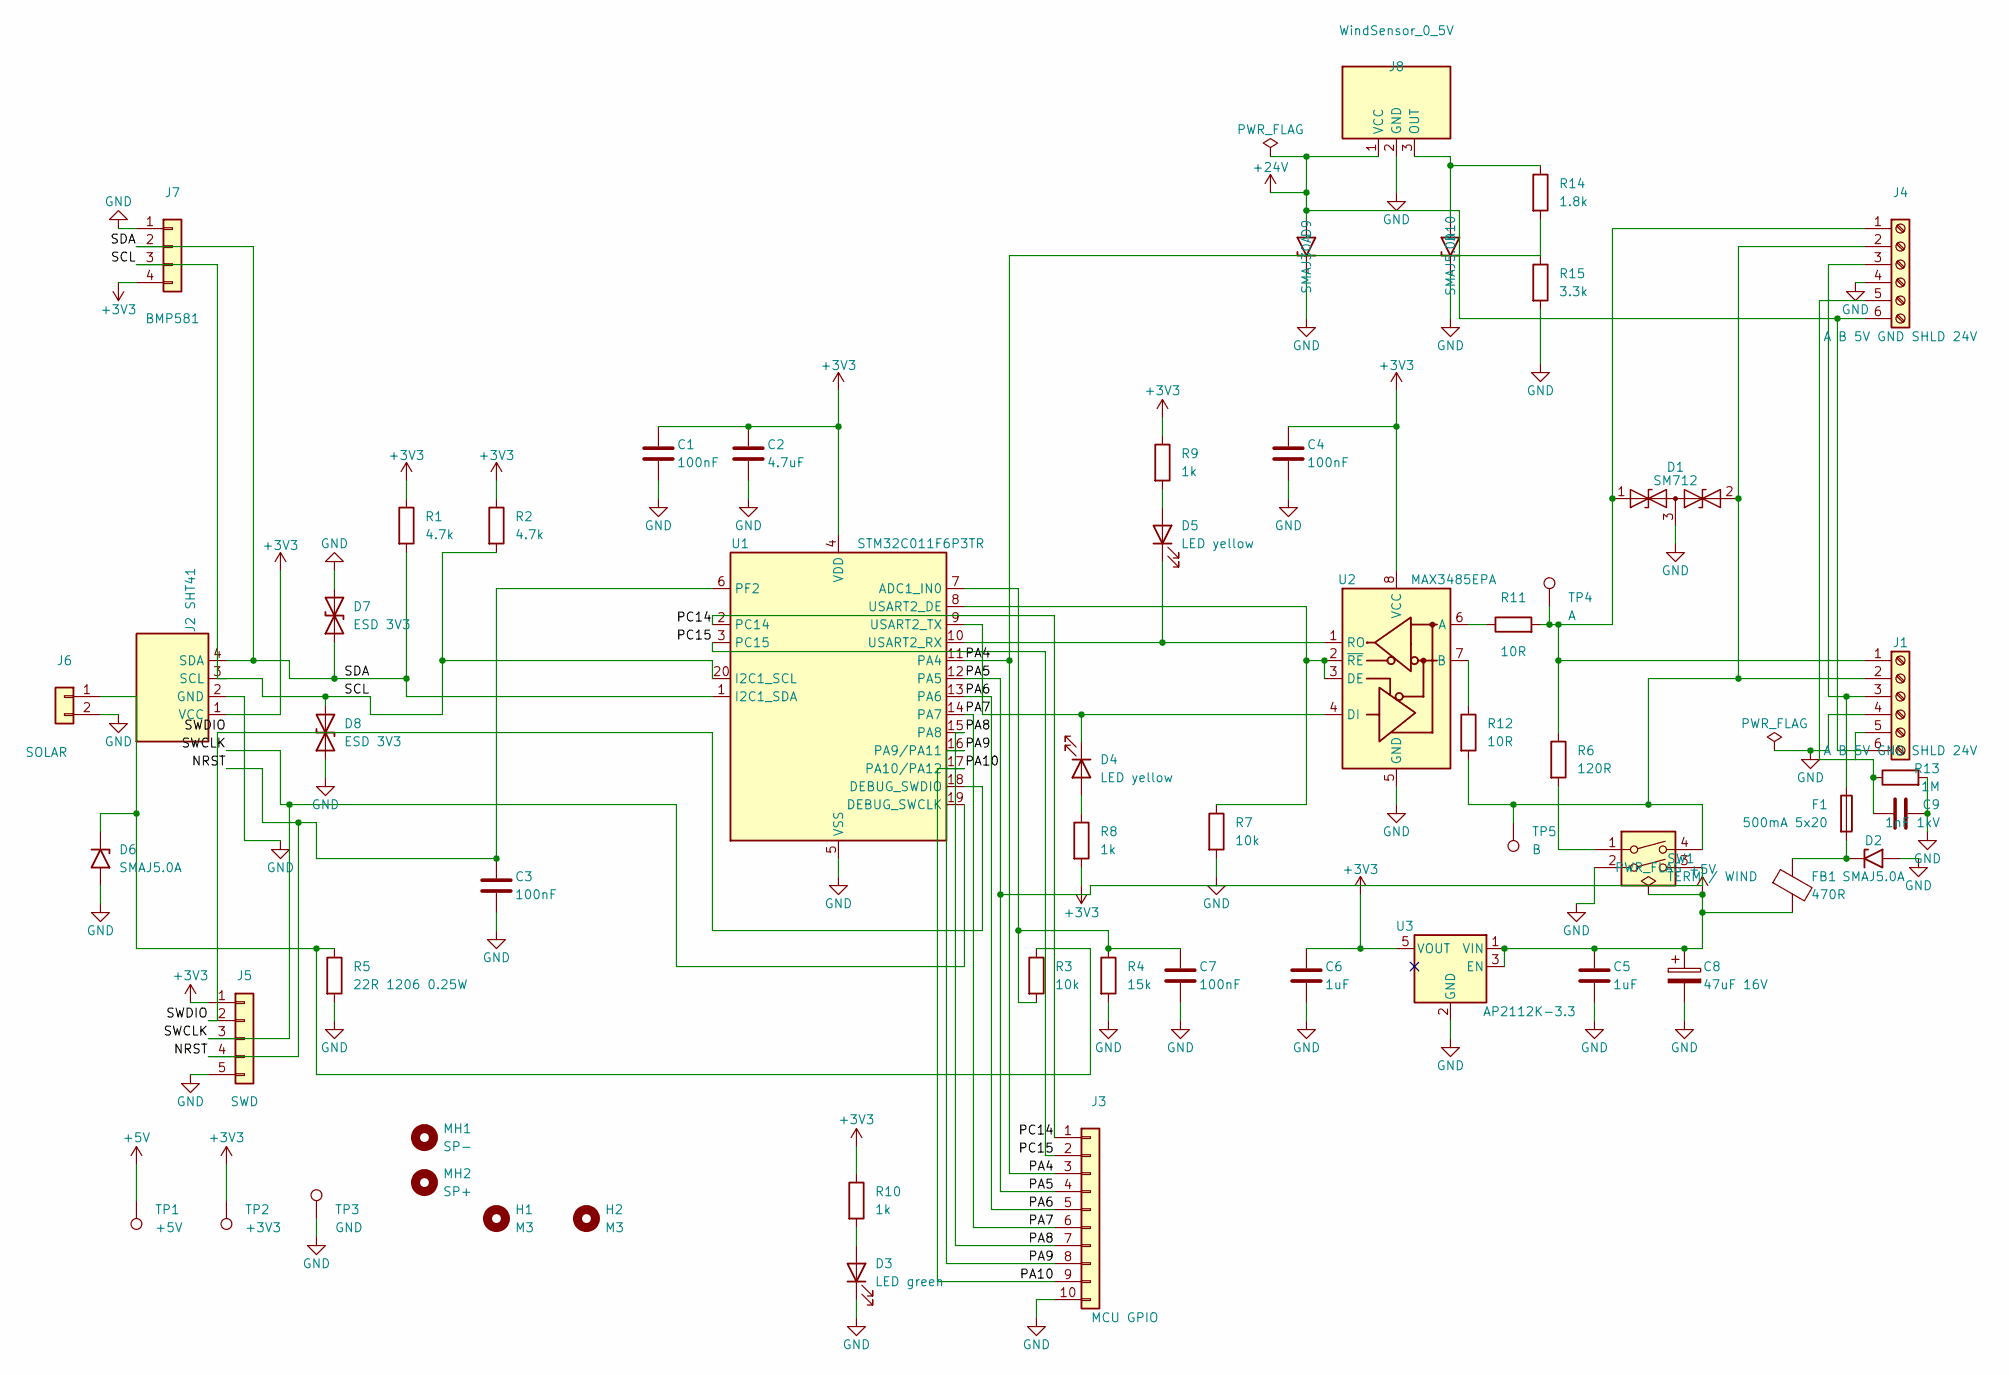
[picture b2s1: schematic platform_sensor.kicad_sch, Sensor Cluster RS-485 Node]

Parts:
C1, C3, C4, C7: 100nF; C_0805_2012Metric
C2: 4.7uF; C_0805_2012Metric
C5, C6: 1uF; C_0805_2012Metric
C8: 47uF 16V; CP_Elec_6.3x5.4
C9: 1nF 1kV; C_1206_3216Metric
D1: SM712; SOT-23
D2, D6, D10: SMAJ5.0A; D_SMA
D3: LED green; LED_0805_2012Metric
D4, D5: LED yellow; LED_0805_2012Metric
D7, D8: ESD 3V3; D_SOD-523
D9: SMAJ30A; D_SMA
F1: 500mA 5x20; FuseHolder_5x20_ELECAPITAL_PCB_Cover
FB1: 470R; L_0805_2012Metric
H1, H2: M3; MountingHole_3.2mm_M3
J1, J4: A B 5V GND SHLD 24V; TerminalBlock_MaiXu_MX126-5.0-06P_1x06_P5.00mm
J2: SHT41; PinHeader_1x04_P2.54mm_Vertical
J3: MCU GPIO; PinHeader_1x10_P2.54mm_Vertical
J5: SWD; PinHeader_1x05_P2.54mm_Vertical
J6: SOLAR; PinHeader_1x02_P2.54mm_Vertical
J7: BMP581; PinHeader_1x04_P2.54mm_Vertical
J8: WindSensor_0_5V; TerminalBlock_MaiXu_MX126-5.0-04P_1x04_P5.00mm
MH1: SP-; MountingHole_2.2mm_M2_DIN965_Pad
MH2: SP+; MountingHole_2.2mm_M2_DIN965_Pad
R1, R2: 4.7k; R_0805_2012Metric
R3, R7: 10k; R_0805_2012Metric
R4: 15k; R_0805_2012Metric
R5: 22R 1206 0.25W; R_1206_3216Metric
R6: 120R; R_0805_2012Metric
R8, R9, R10: 1k; R_0805_2012Metric
R11, R12: 10R; R_1206_3216Metric
R13: 1M; R_0805_2012Metric
R14: 1.8k; R_0805_2012Metric
R15: 3.3k; R_0805_2012Metric
SW1: TERM / WIND; SW_DIP_SPSTx02_Slide_9.78x7.26mm_W7.62mm_P2.54mm
TP1: +5V; TestPoint_THTPad_D2.0mm_Drill1.0mm
TP2: +3V3; TestPoint_THTPad_D2.0mm_Drill1.0mm
TP3: GND; TestPoint_THTPad_D2.0mm_Drill1.0mm
TP4: A; TestPoint_THTPad_D2.0mm_Drill1.0mm
TP5: B; TestPoint_THTPad_D2.0mm_Drill1.0mm
U1: STM32C011F6P3TR; TSSOP-20_4.4x6.5mm_P0.65mm
U2: MAX3485EPA; DIP-8_W7.62mm
U3: AP2112K-3.3; SOT-23-5

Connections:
+3V3: C1.1, C2.1, C4.1, C6.1, J2.1 (VCC), J5.1, J7.4, R1.1, R2.1, R8.2, R9.1, R10.1, TP2.1 (1_1), U1.4 (VDD), U2.8 (VCC), U3.5 (VOUT)
+5V: C5.1, C8.1, FB1.2, TP1.1 (1_1), U3.1 (VIN), U3.3 (EN)
+24V: D9.2 (A2), J1.6, J4.6, J8.1 (VCC)
/NRST: C3.1, J5.4, U1.6 (PF2)
/PA4: J3.3, R14.2, R15.1, U1.11 (PA4)
/PA5: J3.4, SW1.3, U1.12 (PA5)
/PA6: J3.5, U1.13 (PA6)
/PA7: J3.6, U1.14 (PA7)
/PA8: J3.7, U1.15 (PA8)
/PA9: J3.8, U1.16 (PA9/PA11)
/PA10: J3.9, U1.17 (PA10/PA12)
/PC14: J3.1, U1.2 (PC14)
/PC15: J3.2, U1.3 (PC15)
/SCL: D8.2 (A2), J2.3 (SCL), J7.3, R2.2, U1.20 (I2C1_SCL)
/SDA: D7.1 (A1), J2.4 (SDA), J7.2, R1.2, U1.1 (I2C1_SDA)
/SWCLK: J5.3, U1.19 (DEBUG_SWCLK)
/SWDIO: J5.2, U1.18 (DEBUG_SWDIO)
GND: C1.2, C2.2, C3.2, C4.2, C5.2, C6.2, C7.2, C8.2, C9.2, D1.3 (common), D2.2 (A2), D3.1 (K), D6.2 (A2), D7.2 (A2), D8.1 (A1), D9.1 (A1), D10.1 (A1), J1.4, J2.2 (GND), J3.10, J4.4, J5.5, J6.2, J7.1, J8.2 (GND), R4.2, R5.2, R7.2, R13.2, R15.2, SW1.2, TP3.1 (1_1), U1.5 (VSS), U2.5 (GND), U3.2 (GND)
unnamed: D1.1 (A1), J1.1, J4.1, R6.1, R11.2, TP4.1 (1_1)
unnamed: D1.2 (A2), J1.2, J4.2, R12.2, SW1.4, TP5.1 (1_1)
unnamed: D2.1 (A1), F1.2, FB1.1
unnamed: D3.2 (A), R10.2
unnamed: D4.2 (A), R8.1
unnamed: D4.1 (K), U1.9 (USART2_TX), U2.4 (DI)
unnamed: D5.2 (A), R9.2
unnamed: D5.1 (K), U1.10 (USART2_RX), U2.1 (RO)
unnamed: D6.1 (A1), J6.1, R3.1, R5.1
unnamed: D10.2 (A2), J8.3 (OUT), R14.1
unnamed: F1.1, J1.3, J4.3
unnamed: C9.1, J1.5, J4.5, R13.1
unnamed: R6.2, SW1.1
unnamed: C7.1, R3.2, R4.1, U1.7 (ADC1_IN0)
unnamed: R7.1, U1.8 (USART2_DE), U2.2 (~RE), U2.3 (DE)
unnamed: R11.1, U2.6 (A)
unnamed: R12.1, U2.7 (B)

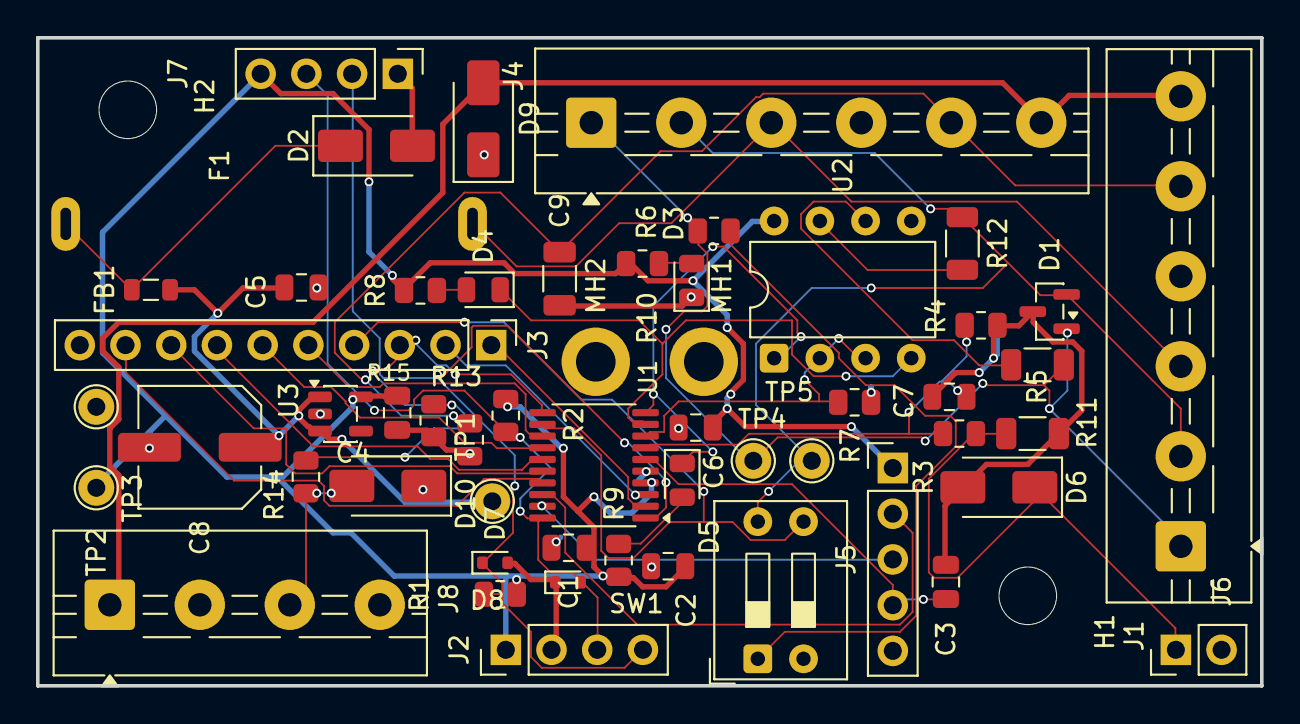
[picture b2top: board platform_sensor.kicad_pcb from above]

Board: 2 copper layers, 68.0 x 36.0 mm, 57 parts (0 on the bottom side), 35 nets.
